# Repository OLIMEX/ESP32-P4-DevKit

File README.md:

# ESP32-P4-DevKit
Development board for ESP32-P4 Dual core RISCV processor from Espressif

https://www.olimex.com/Products/IoT/ESP32-P4/ESP32-P4-DevKit/open-source-hardware

## MIPI-LCD2.8 demos

The ESP-IDF MIPI display demos under `SOFTWARE/Demo_Examples` support both Olimex MIPI-LCD2.8 revisions. They default to WLK2802MIPI-15P-V2. See the per-demo readmes for build instructions and [CHANGELOG.md](CHANGELOG.md) for this revision's configuration changes.

## Licensee
* Hardware is released under CERN Open Hardware Licence Version 2 - Strongly Reciprocal
* Software is released under GPL V3 Licensee
* Documentation is released under CC BY-SA 4.0

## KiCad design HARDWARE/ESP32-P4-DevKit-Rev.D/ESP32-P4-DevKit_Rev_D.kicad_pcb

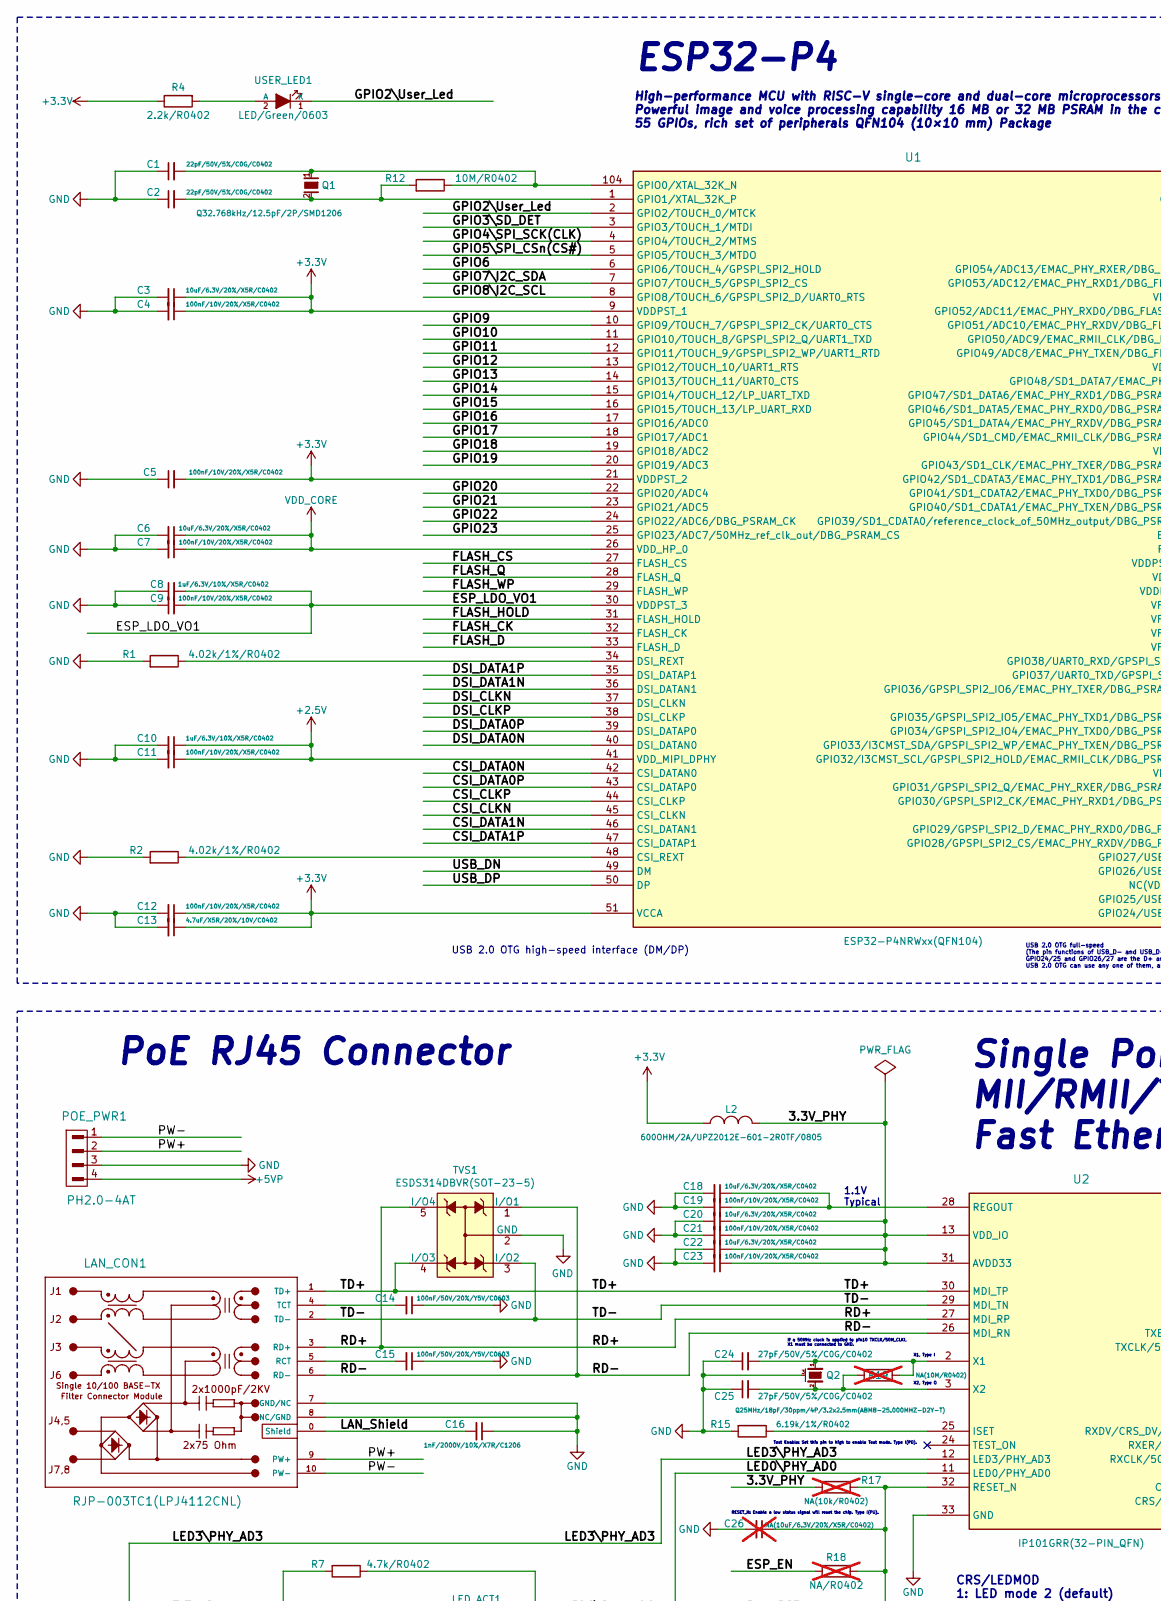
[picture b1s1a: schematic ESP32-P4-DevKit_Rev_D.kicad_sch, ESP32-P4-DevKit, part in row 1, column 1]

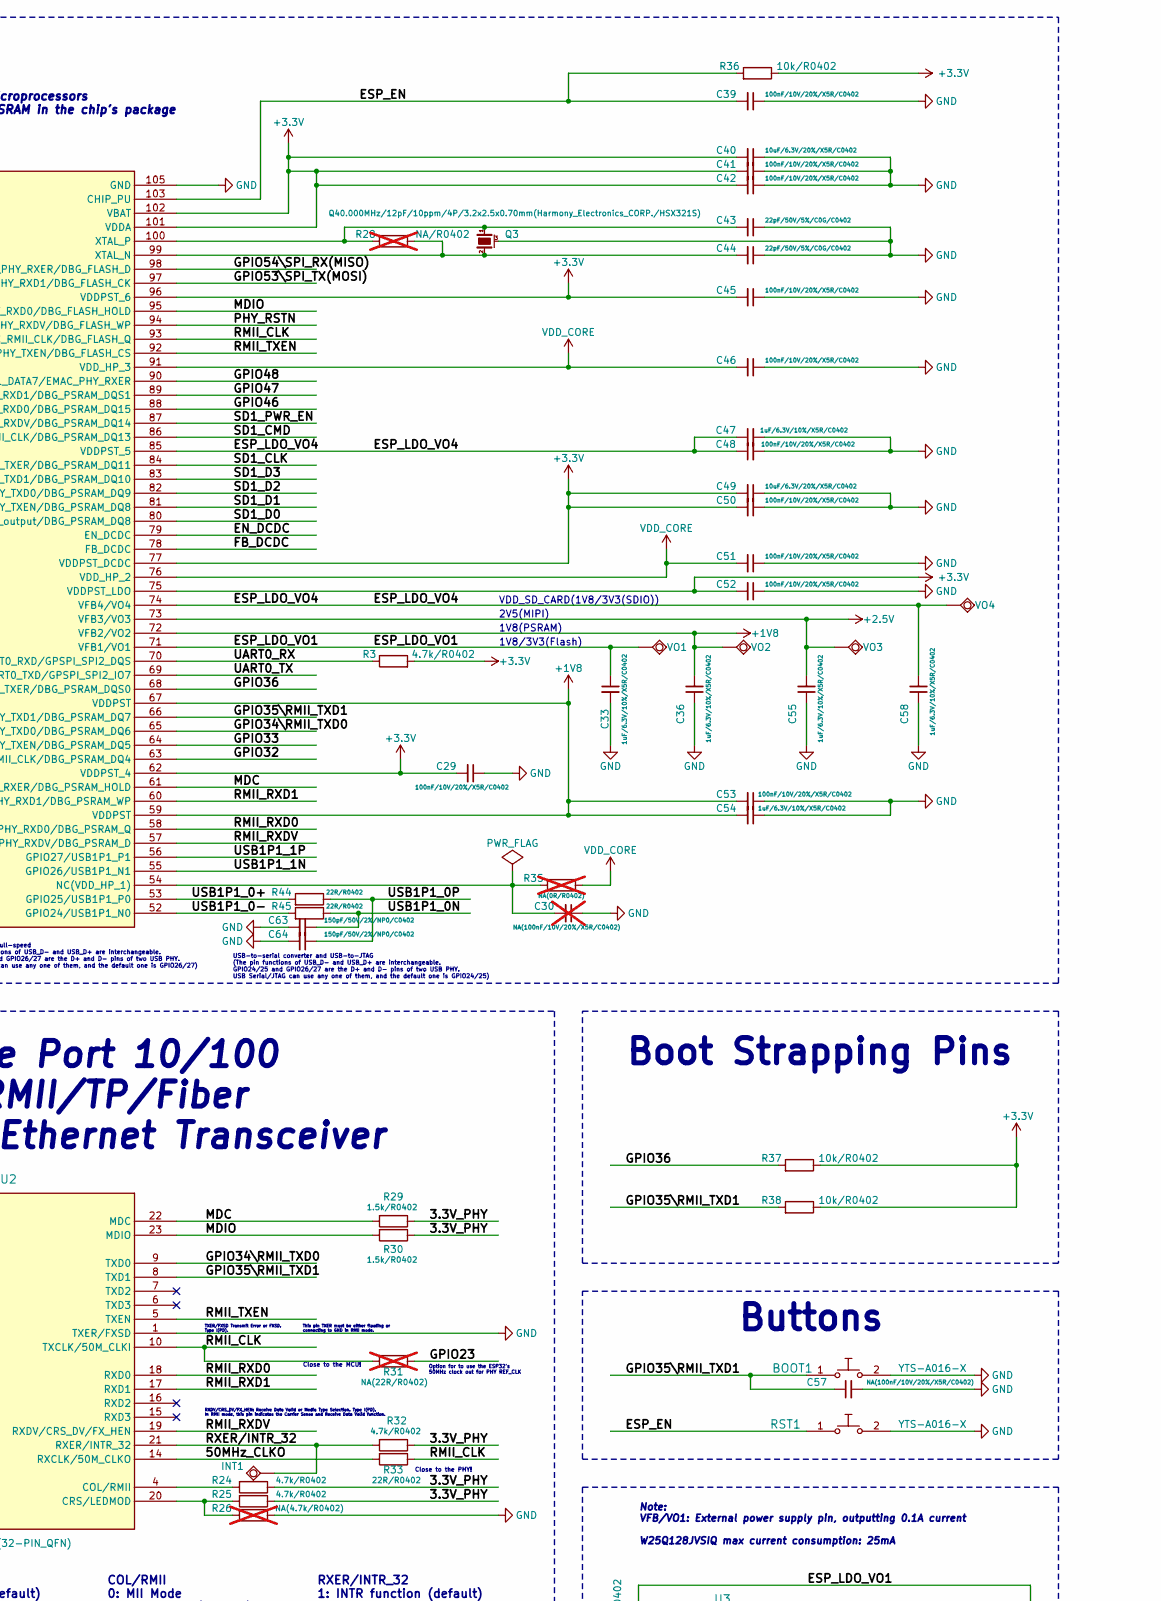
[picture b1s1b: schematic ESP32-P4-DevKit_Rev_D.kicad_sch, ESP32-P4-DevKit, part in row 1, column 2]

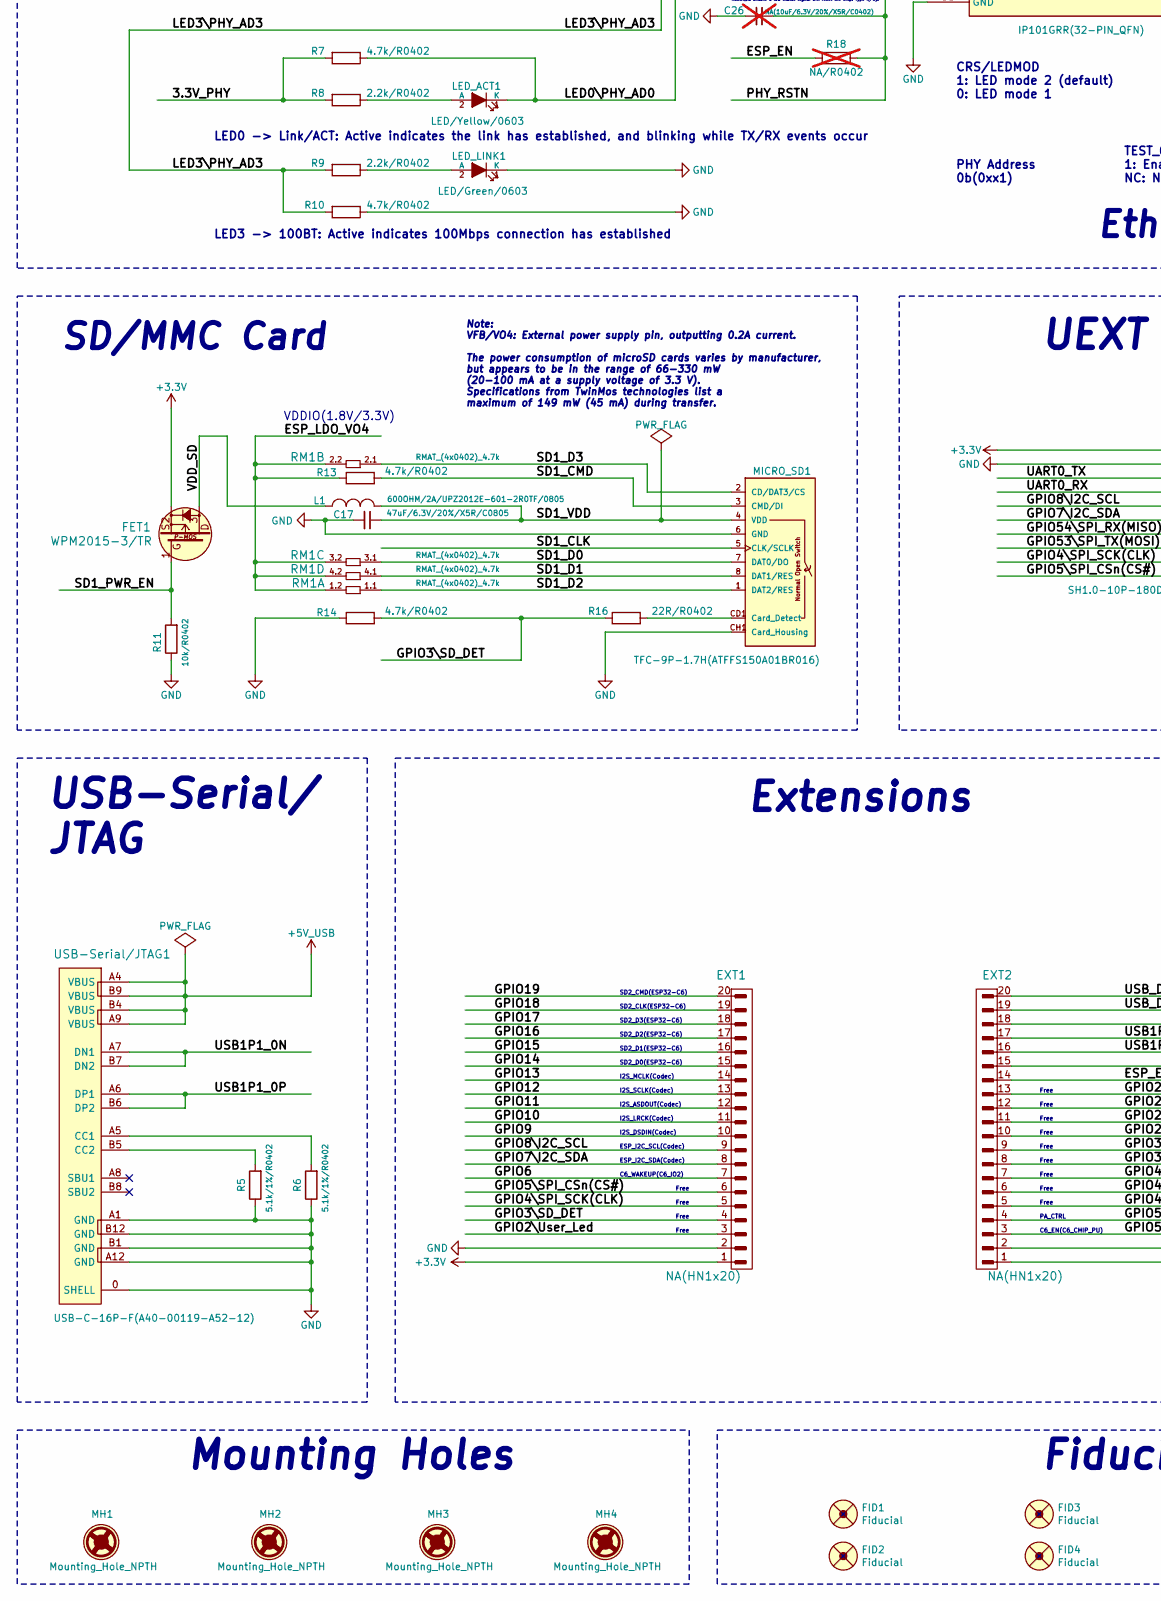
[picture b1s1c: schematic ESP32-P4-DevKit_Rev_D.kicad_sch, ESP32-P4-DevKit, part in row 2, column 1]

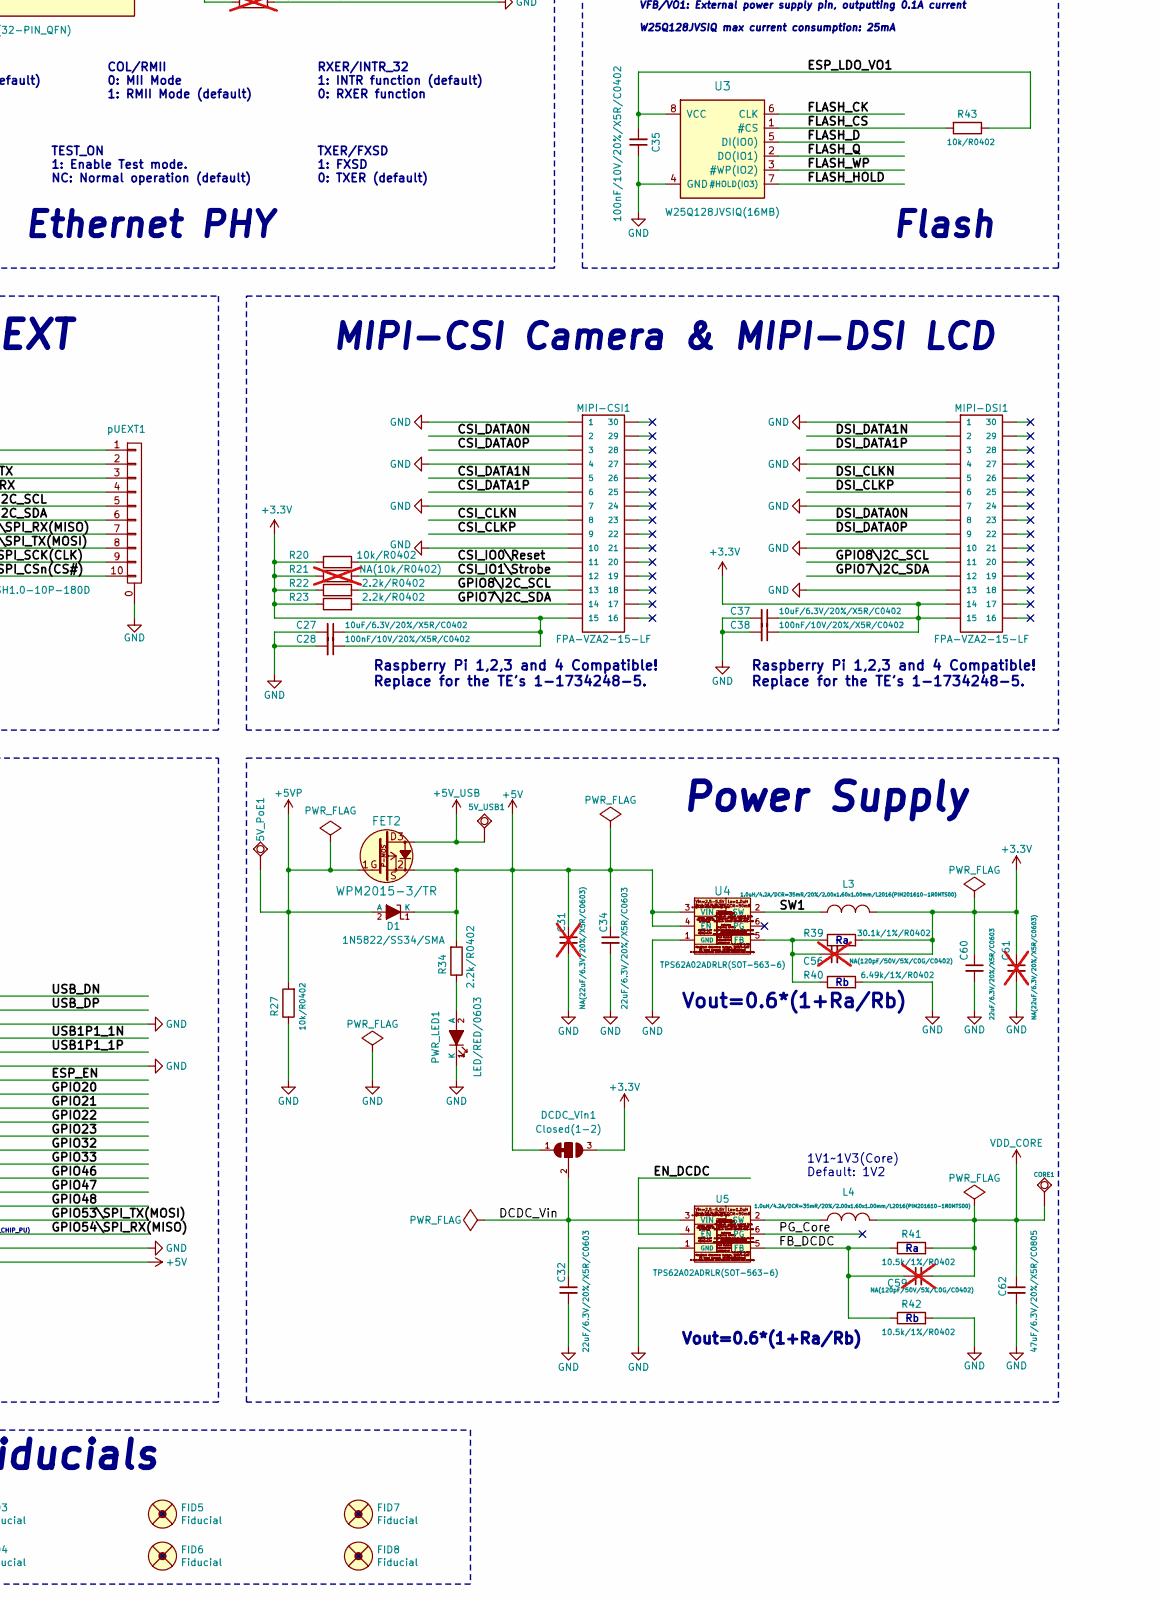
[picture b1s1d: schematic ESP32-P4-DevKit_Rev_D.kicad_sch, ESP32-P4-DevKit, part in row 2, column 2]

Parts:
5V_PoE1, 5V_USB1: TESTPAD; TESTPAD_40-ROUND
BOOT1: YTS-A016-X
C1, C2, C43, C44: 22pF/50V/5%/C0G/C0402; C_0402_5MIL_DWS
C3, C6, C18, C20, C22, C27, C37, C40, C49: 10uF/6.3V/20%/X5R/C0402; C_0402_5MIL_DWS
C4, C5, C7, C9, C11, C12, C19, C21, C23, C28, C29, C35, C38, C39, C41, C42, C45, C46, C48, C50, C51, C52, C53: 100nF/10V/20%/X5R/C0402; C_0402_5MIL_DWS
C8, C10, C33, C36, C47, C54, C55, C58: 1uF/6.3V/10%/X5R/C0402; C_0402_5MIL_DWS
C13: 4.7uF/X5R/20%/10V/C0402; C_0402_5MIL_DWS
C14, C15: 100nF/50V/20%/Y5V/C0603; C_0603_5MIL_DWS
C16: 1nF/2000V/10%/X7R/C1206; C_1206_5MIL_DWS_ISO
C17, C62: 47uF/6.3V/20%/X5R/C0805; C_0805_5MIL_DWS
C24, C25: 27pF/50V/5%/C0G/C0402; C_0402_5MIL_DWS
C26: NA(10uF/6.3V/20%/X5R/C0402); C_0402_5MIL_DWS; not fitted
C30: NA(100nF/10V/20%/X5R/C0402); C_0402_5MIL_DWS; not fitted
C31, C61: NA(22uF/6.3V/20%/X5R/C0603); C_0603_5MIL_DWS; not fitted
C32, C34, C60: 22uF/6.3V/20%/X5R/C0603; C_0603_5MIL_DWS
C56, C59: NA(120pF/50V/5%/C0G/C0402); C_0402_5MIL_DWS; not fitted
C57: NA(100nF/10V/20%/X5R/C0402); C_0402_5MIL_DWS
C63, C64: 150pF/50V/2%/NP0/C0402; C_0402_5MIL_DWS
CORE1: TESTPAD; TESTPAD_40-ROUND
D1: 1N5822/SS34/SMA; SMA-KA
DCDC_Vin1: Closed(1-2); SJ_2_SMALL_12_TIED
EXT1, EXT2: NA(HN1x20); HN1x20
FET1, FET2: WPM2015-3/TR; SOT23
FID1, FID3, FID5, FID7: Fiducial; Fiducial1x3
FID2, FID4, FID6, FID8: Fiducial; Fiducial1x3_Paste
INT1: TESTPAD; TESTPAD_40-ROUND
L1, L2: 600OHM/2A/UPZ2012E-601-2R0TF/0805; L_0805_5MIL_DWS
L3, L4: 1.0uH/4.2A/DCR=35mR/20%/2.00x1.60x1.00mm/L2016(PI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; L_2016_MM
LAN_CON1: RJP-003TC1(LPJ4112CNL)
LED_ACT1: LED/Yellow/0603; LED_0603_KA
LED_LINK1: LED/Green/0603; LED_0603_KA
MH1, MH2, MH3, MH4: Mounting_Hole_NPTH; Mounting_Hole_Drill-3.3mm_Clerance-7mm
MICRO_SD1: TFC-9P-1.7H(ATFFS150A01BR016); uSD(TFC-9P-1.xH(ATFFS150A01BR016))
MIPI-CSI1: FPA-VZA2-15-LF; TE_1-1734248-5
MIPI-DSI1: FPA-VZA2-15-LF; TE_1-1734248-5
POE_PWR1: PH2.0-4AT; PH2.0-4PLB
PWR_LED1: LED/RED/0603; LED_0603_KA
Q1: Q32.768kHz/12.5pF/2P/SMD1206; CM7V-T1A(Crystal_Package-1206_3.20x1.50x0.65mm)
Q2: Q25MHz/18pF/30ppm/4P/3.2x2.5mm(ABM8-25.000MHZ-D2Y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; TSX-3.2x2.5mm_GND(3)
Q3: Q40.000MHz/12pF/10ppm/4P/3.2x2.5x0.70mm(Harmony_E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; TSX-3.2x2.5mm_GND(3)
R1, R2: 4.02k/1%/R0402; R_0402_5MIL_DWS
R3, R7, R10, R13, R14, R24, R25, R32: 4.7k/R0402; R_0402_5MIL_DWS
R4, R8, R9, R22, R23, R34: 2.2k/R0402; R_0402_5MIL_DWS
R5, R6: 5.1k/1%/R0402; R_0402_5MIL_DWS
R11, R20, R27, R36, R37, R38, R43: 10k/R0402; R_0402_5MIL_DWS
R12: 10M/R0402; R_0402_5MIL_DWS
R15: 6.19k/1%/R0402; R_0402_5MIL_DWS
R16, R33, R44, R45: 22R/R0402; R_0402_5MIL_DWS
R17, R21: NA(10k/R0402); R_0402_5MIL_DWS; not fitted
R18, R28: NA/R0402; R_0402_5MIL_DWS; not fitted
R19: NA(10M/R0402); R_0402_5MIL_DWS; not fitted
R26: NA(4.7k/R0402); R_0402_5MIL_DWS; not fitted
R29, R30: 1.5k/R0402; R_0402_5MIL_DWS
R31: NA(22R/R0402); R_0402_5MIL_DWS; not fitted
R35: NA(0R/R0402); R_0402_5MIL_DWS; not fitted
R39: 30.1k/1%/R0402; R_0402_5MIL_DWS
R40: 6.49k/1%/R0402; R_0402_5MIL_DWS
R41, R42: 10.5k/1%/R0402; R_0402_5MIL_DWS
RM1: RMAT_(4x0402)_4.7k; RA0805_(4X0402)_xx_BIGGEROUTPADS
RST1: YTS-A016-X
TVS1: ESDS314DBVR(SOT-23-5); SOT-23-5
U1: ESP32-P4NRWxx(QFN104); QFN104_10mm×10mm_Pitch_0.35mm
U2: IP101GRR(32-PIN_QFN); QFN32_EP(33)_4.00x4.00x0.80mm_Pitch_0.40mm
U3: W25Q128JVSIQ(16MB); SO-8_208mil
U4, U5: TPS62A02ADRLR(SOT-563-6); SOT-563-6
USB-Serial/JTAG1: USB-C-16P-F(A40-00119-A52-12); USB2.0_TYPE-C(A40-00119-A52-12)_Paste
USER_LED1: LED/Green/0603; LED_0603_KA
VO1, VO2, VO3, VO4: TESTPAD; TESTPAD_40-ROUND
pUEXT1: SH1.0-10P-180D; BM10B-SRSS-TB

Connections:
+1V8: C36.2, C53.2, C54.2, U1.59 (VDDPST), U1.67 (VDDPST), U1.72 (VFB2/VO2), VO2.1 (Pad)
+2.5V: C10.1, C11.1, C55.2, U1.41 (VDD_MIPI_DPHY), U1.73 (VFB3/VO3), VO3.1 (Pad)
+3.3V: C3.1, C4.1, C5.2, C12.1, C13.1, C27.1, C28.1, C29.2, C37.1, C38.1, C40.2, C41.2, C42.2, C45.2, C49.2, C50.2, C52.2, C56.2, C60.1, C61.1, DCDC_Vin1.3, EXT1.1, FET1.2, L2.1, L3.2, MIPI-CSI1.15, MIPI-DSI1.14, MIPI-DSI1.15, R3.2, R4.1, R20.1, R21.1, R22.1, R23.1, R36.1, R37.1, R38.1, R39.2, U1.9 (VDDPST_1), U1.21 (VDDPST_2), U1.51 (VCCA), U1.62 (VDDPST_4), U1.75 (VDDPST_LDO), U1.77 (VDDPST_DCDC), U1.96 (VDDPST_6), U1.101 (VDDA), U1.102 (VBAT), pUEXT1.1
+5V: C31.1, C34.1, D1.1 (K), DCDC_Vin1.1, EXT2.1, FET2.2, R34.2, U4.3 (VIN), U4.4 (EN)
+5VP: 5V_PoE1.1 (Pad), D1.2 (A), FET2.1, POE_PWR1.4, R27.2
+5V_USB: 5V_USB1.1 (Pad), FET2.3, USB-Serial/JTAG1.A4 (VBUS), USB-Serial/JTAG1.A9 (VBUS), USB-Serial/JTAG1.B4 (VBUS), USB-Serial/JTAG1.B9 (VBUS)
/3.3V_PHY: C20.1, C21.1, C22.1, C23.1, L2.2, R7.2, R8.2, R17.1, R24.1, R25.1, R29.1, R30.1, R32.1, U2.13 (VDD_IO), U2.31 (AVDD33)
/50MHz_CLKO: R33.2, U2.14 (RXCLK/50M_CLKO)
/CSI_CLKN: MIPI-CSI1.8, U1.45 (CSI_CLKN)
/CSI_CLKP: MIPI-CSI1.9, U1.44 (CSI_CLKP)
/CSI_DATA0N: MIPI-CSI1.2, U1.42 (CSI_DATAN0)
/CSI_DATA0P: MIPI-CSI1.3, U1.43 (CSI_DATAP0)
/CSI_DATA1N: MIPI-CSI1.5, U1.46 (CSI_DATAN1)
/CSI_DATA1P: MIPI-CSI1.6, U1.47 (CSI_DATAP1)
/CSI_IO0\Reset: MIPI-CSI1.11, R20.2
/CSI_IO1\Strobe: MIPI-CSI1.12, R21.2
/DCDC_Vin: C32.1, DCDC_Vin1.2, U5.3 (VIN)
/DSI_CLKN: MIPI-DSI1.5, U1.37 (DSI_CLKN)
/DSI_CLKP: MIPI-DSI1.6, U1.38 (DSI_CLKP)
/DSI_DATA0N: MIPI-DSI1.8, U1.40 (DSI_DATAN0)
/DSI_DATA0P: MIPI-DSI1.9, U1.39 (DSI_DATAP0)
/DSI_DATA1N: MIPI-DSI1.2, U1.36 (DSI_DATAN1)
/DSI_DATA1P: MIPI-DSI1.3, U1.35 (DSI_DATAP1)
/EN_DCDC: U1.79 (EN_DCDC), U5.4 (EN)
/ESP_EN: C39.2, EXT2.14, R18.1, R36.2, RST1.1, U1.103 (CHIP_PU)
/ESP_LDO_VO1: C8.2, C9.2, C33.1, C35.2, R43.1, U1.30 (VDDPST_3), U1.71 (VFB1/VO1), U3.8 (VCC), VO1.1 (Pad)
/ESP_LDO_VO4: C47.1, C48.1, C58.2, R13.1, RM1.1.2, RM1.2.2, RM1.3.2, RM1.4.2, U1.74 (VFB4/VO4), U1.85 (VDDPST_5), VO4.1 (Pad)
/FB_DCDC: C59.1, R41.1, R42.1, U1.78 (FB_DCDC), U5.5 (FB)
/FLASH_CK: U1.32 (FLASH_CK), U3.6 (CLK)
/FLASH_CS: R43.2, U1.27 (FLASH_CS), U3.1 (#CS)
/FLASH_D: U1.33 (FLASH_D), U3.5 (DI(IO0))
/FLASH_HOLD: U1.31 (FLASH_HOLD), U3.7 (#HOLD(IO3))
/FLASH_Q: U1.28 (FLASH_Q), U3.2 (DO(IO1))
/FLASH_WP: U1.29 (FLASH_WP), U3.3 (#WP(IO2))
/GPIO2\User_Led: EXT1.3, U1.2 (GPIO2/TOUCH_0/MTCK), USER_LED1.1 (K)
/GPIO3\SD_DET: EXT1.4, R14.2, R16.1, U1.3 (GPIO3/TOUCH_1/MTDI)
/GPIO4\SPI_SCK(CLK): EXT1.5, U1.4 (GPIO4/TOUCH_2/MTMS), pUEXT1.9
/GPIO5\SPI_CSn(CS#): EXT1.6, U1.5 (GPIO5/TOUCH_3/MTDO), pUEXT1.10
/GPIO6: EXT1.7, U1.6 (GPIO6/TOUCH_4/GPSPI_SPI2_HOLD)
/GPIO7\I2C_SDA: EXT1.8, MIPI-CSI1.14, MIPI-DSI1.12, R23.2, U1.7 (GPIO7/TOUCH_5/GPSPI_SPI2_CS), pUEXT1.6
/GPIO8\I2C_SCL: EXT1.9, MIPI-CSI1.13, MIPI-DSI1.11, R22.2, U1.8 (GPIO8/TOUCH_6/GPSPI_SPI2_D/UART0_RTS), pUEXT1.5
/GPIO9: EXT1.10, U1.10 (GPIO9/TOUCH_7/GPSPI_SPI2_CK/UART0_CTS)
/GPIO10: EXT1.11, U1.11 (GPIO10/TOUCH_8/GPSPI_SPI2_Q/UART1_TXD)
/GPIO11: EXT1.12, U1.12 (GPIO11/TOUCH_9/GPSPI_SPI2_WP/UART1_RTD)
/GPIO12: EXT1.13, U1.13 (GPIO12/TOUCH_10/UART1_RTS)
/GPIO13: EXT1.14, U1.14 (GPIO13/TOUCH_11/UART0_CTS)
/GPIO14: EXT1.15, U1.15 (GPIO14/TOUCH_12/LP_UART_TXD)
/GPIO15: EXT1.16, U1.16 (GPIO15/TOUCH_13/LP_UART_RXD)
/GPIO16: EXT1.17, U1.17 (GPIO16/ADC0)
/GPIO17: EXT1.18, U1.18 (GPIO17/ADC1)
/GPIO18: EXT1.19, U1.19 (GPIO18/ADC2)
/GPIO19: EXT1.20, U1.20 (GPIO19/ADC3)
/GPIO20: EXT2.13, U1.22 (GPIO20/ADC4)
/GPIO21: EXT2.12, U1.23 (GPIO21/ADC5)
/GPIO22: EXT2.11, U1.24 (GPIO22/ADC6/DBG_PSRAM_CK)
/GPIO23: EXT2.10, R31.1, U1.25 (GPIO23/ADC7/50MHz_ref_clk_out/DBG_PSRAM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)
/GPIO32: EXT2.9, U1.63 (GPIO32/I3CMST_SCL/GPSPI_SPI2_HOLD/EMAC_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)
/GPIO33: EXT2.8, U1.64 (GPIO33/I3CMST_SDA/GPSPI_SPI2_WP/EMAC_PH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)
/GPIO34\RMII_TXD0: U1.65 (GPIO34/GPSPI_SPI2_IO4/EMAC_PHY_TXD0/DBG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), U2.9 (TXD0)
/GPIO35\RMII_TXD1: BOOT1.1, C57.1, R38.2, U1.66 (GPIO35/GPSPI_SPI2_IO5/EMAC_PHY_TXD1/DBG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), U2.8 (TXD1)
/GPIO36: R37.2, U1.68 (GPIO36/GPSPI_SPI2_IO6/EMAC_PHY_TXER/DBG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)
/GPIO46: EXT2.7, U1.88 (GPIO46/SD1_DATA5/EMAC_PHY_RXD0/DBG_PSRA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)
/GPIO47: EXT2.6, U1.89 (GPIO47/SD1_DATA6/EMAC_PHY_RXD1/DBG_PSRA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)
/GPIO48: EXT2.5, U1.90 (GPIO48/SD1_DATA7/EMAC_PHY_RXER)
/GPIO53\SPI_TX(MOSI): EXT2.4, U1.97 (GPIO53/ADC12/EMAC_PHY_RXD1/DBG_FLASH_CK), pUEXT1.8
/GPIO54\SPI_RX(MISO): EXT2.3, U1.98 (GPIO54/ADC13/EMAC_PHY_RXER/DBG_FLASH_D), pUEXT1.7
/LAN_Shield: C16.2, LAN_CON1.0 (Shield)
/LED0\PHY_AD0: LED_ACT1.1 (K), R7.1, U2.11 (LED0/PHY_AD0)
/LED3\PHY_AD3: R9.2, R10.2, U2.12 (LED3/PHY_AD3)
/MDC: R29.2, U1.61 (GPIO31/GPSPI_SPI2_Q/EMAC_PHY_RXER/DBG_P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), U2.22 (MDC)
/MDIO: R30.2, U1.95 (GPIO52/ADC11/EMAC_PHY_RXD0/DBG_FLASH_HO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), U2.23 (MDIO)
/PG_Core: U5.6 (PG)
/PHY_RSTN: C26.1, R17.2, R18.2, U1.94 (GPIO51/ADC10/EMAC_PHY_RXDV/DBG_FLASH_WP), U2.32 (RESET_N)
/PW+: LAN_CON1.9 (PW+), POE_PWR1.2
/PW-: LAN_CON1.10 (PW-), POE_PWR1.1
/RD+: LAN_CON1.3 (RD+), TVS1.5 (I/O4), U2.27 (MDI_RP)
/RD-: LAN_CON1.6 (RD-), TVS1.1 (I/O1), U2.26 (MDI_RN)
/RMII_CLK: R31.2, R33.1, U1.93 (GPIO50/ADC9/EMAC_RMII_CLK/DBG_FLASH_Q), U2.10 (TXCLK/50M_CLKI)
/RMII_RXD0: U1.58 (GPIO29/GPSPI_SPI2_D/EMAC_PHY_RXD0/DBG_P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), U2.18 (RXD0)
/RMII_RXD1: U1.60 (GPIO30/GPSPI_SPI2_CK/EMAC_PHY_RXD1/DBG_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), U2.17 (RXD1)
/RMII_RXDV: U1.57 (GPIO28/GPSPI_SPI2_CS/EMAC_PHY_RXDV/DBG_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), U2.19 (RXDV/CRS_DV/FX_HEN)
/RMII_TXEN: U1.92 (GPIO49/ADC8/EMAC_PHY_TXEN/DBG_FLASH_CS), U2.5 (TXEN)
/RXER/INTR_32: INT1.1 (Pad), R32.2, U2.21 (RXER/INTR_32)
/SD1_CLK: MICRO_SD1.5 (CLK/SCLK), U1.84 (GPIO43/SD1_CLK/EMAC_PHY_TXER/DBG_PSRAM_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)
/SD1_CMD: MICRO_SD1.3 (CMD/DI), R13.2, U1.86 (GPIO44/SD1_CMD/EMAC_RMII_CLK/DBG_PSRAM_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)
/SD1_D0: MICRO_SD1.7 (DAT0/DO), RM1.3.1, U1.80 (GPIO39/SD1_CDATA0/reference_clock_of_50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)
/SD1_D1: MICRO_SD1.8 (DAT1/RES), RM1.4.1, U1.81 (GPIO40/SD1_CDATA1/EMAC_PHY_TXEN/DBG_PSR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)
/SD1_D2: MICRO_SD1.1 (DAT2/RES), RM1.1.1, U1.82 (GPIO41/SD1_CDATA2/EMAC_PHY_TXD0/DBG_PSR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)
/SD1_D3: MICRO_SD1.2 (CD/DAT3/CS), RM1.2.1, U1.83 (GPIO42/SD1_CDATA3/EMAC_PHY_TXD1/DBG_PSR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)
/SD1_PWR_EN: FET1.1, R11.2, U1.87 (GPIO45/SD1_DATA4/EMAC_PHY_RXDV/DBG_PSRA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)
/SD1_VDD: C17.1, L1.2, MICRO_SD1.4 (VDD)
/SW1: L3.1, U4.2 (SW)
/TD+: LAN_CON1.1 (TD+), TVS1.4 (I/O3), U2.30 (MDI_TP)
/TD-: LAN_CON1.2 (TD-), TVS1.3 (I/O2), U2.29 (MDI_TN)
/UART0_RX: R3.1, U1.70 (GPIO38/UART0_RXD/GPSPI_SPI2_DQS), pUEXT1.4
/UART0_TX: U1.69 (GPIO37/UART0_TXD/GPSPI_SPI2_IO7), pUEXT1.3
/USB1P1_0+: R44.2, U1.53 (GPIO25/USB1P1_P0)
/USB1P1_0-: R45.2, U1.52 (GPIO24/USB1P1_N0)
/USB1P1_0N: C63.1, R45.1, USB-Serial/JTAG1.A7 (DN1), USB-Serial/JTAG1.B7 (DN2)
/USB1P1_0P: C64.1, R44.1, USB-Serial/JTAG1.A6 (DP1), USB-Serial/JTAG1.B6 (DP2)
/USB1P1_1N: EXT2.17, U1.55 (GPIO26/USB1P1_N1)
/USB1P1_1P: EXT2.16, U1.56 (GPIO27/USB1P1_P1)
/USB_DN: EXT2.20, U1.49 (DM)
/USB_DP: EXT2.19, U1.50 (DP)
/VDD_SD: FET1.3, L1.1
GND: BOOT1.2, C1.1, C2.1, C3.2, C4.2, C5.1, C6.2, C7.2, C8.1, C9.1, C10.2, C11.2, C12.2, C13.2, C14.1, C15.1, C16.1, C17.2, C18.2, C19.2, C20.2, C21.2, C22.2, C23.2, C24.1, C25.1, C26.2, C27.2, C28.2, C29.1, C30.1, C31.2, C32.2, C33.2, C34.2, C35.1, C36.1, C37.2, C38.2, C39.1, C40.1, C41.1, C42.1, C43.1, C44.1, C45.1, C46.1, C47.2, C48.2, C49.1, C50.1, C51.1, C52.1, C53.1, C54.1, C55.1, C57.2, C58.1, C60.2, C61.2, C62.2, C63.2, C64.2, EXT1.2, EXT2.2, EXT2.15, EXT2.18, LAN_CON1.7 (GND/NC), LAN_CON1.8 (NC/GND), LED_LINK1.1 (K), MICRO_SD1.6 (GND), MICRO_SD1.CH1 (Card_Housing), MIPI-CSI1.1, MIPI-CSI1.4, MIPI-CSI1.7, MIPI-CSI1.10, MIPI-DSI1.1, MIPI-DSI1.4, MIPI-DSI1.7, MIPI-DSI1.10, MIPI-DSI1.13, POE_PWR1.3, PWR_LED1.1 (K), Q2.3 (case), Q3.3 (case), R1.2, R2.2, R5.1, R6.1, R10.1, R11.1, R14.1, R15.2, R26.1, R27.1, R40.2, R42.2, RST1.2, TVS1.2 (GND), U1.105 (GND), U2.1 (TXER/FXSD), U2.33 (GND), U3.4 (GND), U4.1 (GND), U5.1 (GND), USB-Serial/JTAG1.0 (SHELL), USB-Serial/JTAG1.A1 (GND), USB-Serial/JTAG1.A12 (GND), USB-Serial/JTAG1.B1 (GND), USB-Serial/JTAG1.B12 (GND), pUEXT1.0, pUEXT1.2
unnamed: C15.2, LAN_CON1.5 (RCT)
unnamed: C14.2, LAN_CON1.4 (TCT)
unnamed: LED_ACT1.2 (A), R8.1
unnamed: LED_LINK1.2 (A), R9.1
unnamed: MICRO_SD1.CD1 (Card_Detect), R16.2
unnamed: PWR_LED1.2 (A), R34.1
unnamed: R2.1, U1.48 (CSI_REXT)
unnamed: R1.1, U1.34 (DSI_REXT)
unnamed: C1.2, Q1.1, R12.1, U1.104 (GPIO0/XTAL_32K_N)
unnamed: C2.2, Q1.2, R12.2, U1.1 (GPIO1/XTAL_32K_P)
unnamed: C30.2, R35.2, U1.54 (NC(VDD_HP_1))
unnamed: C44.2, Q3.2, R28.2, U1.99 (XTAL_N)
unnamed: C43.2, Q3.1, R28.1, U1.100 (XTAL_P)
unnamed: R24.2, U2.4 (COL/RMII)
unnamed: R25.2, R26.2, U2.20 (CRS/LEDMOD)
unnamed: R15.1, U2.25 (ISET)
unnamed: C18.1, C19.1, U2.28 (REGOUT)
unnamed: C24.2, Q2.1, R19.2, U2.2 (X1)
unnamed: C25.2, Q2.2, R19.1, U2.3 (X2)
unnamed: C56.1, R39.1, R40.1, U4.5 (FB)
unnamed: L4.1, U5.2 (SW)
unnamed: R6.2, USB-Serial/JTAG1.A5 (CC1)
unnamed: R5.2, USB-Serial/JTAG1.B5 (CC2)
unnamed: R4.2, USER_LED1.2 (A)
VDD_CORE: C6.1, C7.1, C46.2, C51.2, C59.2, C62.1, CORE1.1 (Pad), L4.2, R35.1, R41.2, U1.26 (VDD_HP_0), U1.76 (VDD_HP_2), U1.91 (VDD_HP_3)

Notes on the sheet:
Note: VFB/VO1: External power supply pin, outputting 0.1A current W25Q128JVSIQ max current consumption: 25mA
TXER/FXSD Transmit Error or FXSD. Type I(PD).
I2S_LRCK(Codec)
USB-to-serial converter and USB-to-JTAG (The pin functions of USB_D- and USB_D+ are interchangeable. GPIO24/25 and GPIO26/27 are the D+ and D- pins of two USB PHY. USB Serial/JTAG can use any one of them, and the default one is GPIO24/25)
Power Supply
Vout=0.6*(1+Ra/Rb)
I2S_DSDIN(Codec)
Free
SD2_D2(ESP32-C6)
Boot Strapping Pins
Mounting Holes
LED0 -> Link/ACT: Active indicates the link has established, and blinking while TX/RX events occur
SD2_D1(ESP32-C6)
RXER/INTR_32 1: INTR function (default) 0: RXER function
COL/RMII 0: MII Mode 1: RMII Mode (default)
This pin TXER must be either floating or connecting to GND in RMII mode.
I2S_SCLK(Codec)
Close to the MCU!
RXDV/CRS_DV/FX_HEN: Receive Data Valid or Media Type Selection. Type I(PD). In RMII mode, this pin indicates the Carrier Sense and Receive Data Valid function.
SD2_CLK(ESP32-C6)
TXER/FXSD 1: FXSD 0: TXER (default)
TEST_ON 1: Enable Test mode. NC: Normal operation (default)
Ethernet PHY
SD2_CMD(ESP32-C6)
Test Enable: Set this pin to high to enable Test mode. Type I(PD).
High-performance MCU with RISC-V single-core and dual-core microprocessors Powerful image and voice processing capability 16 MB or 32 MB PSRAM in the chip's package 55 GPIOs, rich set of peripherals QFN104 (10×10 mm) Package
USB 2.0 OTG high-speed interface (DM/DP)
If a 50MHz clock is applied to pin10 TXCLK/50M_CLKI, X1 must be connected to GND.
1V8/3V3(Flash)
X2, Type O
SD2_D0(ESP32-C6)
PoE RJ45 Connector
MIPI-CSI Camera & MIPI-DSI LCD
Raspberry Pi 1,2,3 and 4 Compatible! Replace for the TE's 1-1734248-5.
RESET_N: Enable a low status signal will reset the chip. Type I(PU).
I2S_ASDOUT(Codec)
C6_WAKEUP(C6_IO2)
USB 2.0 OTG full-speed (The pin functions of USB_D- and USB_D+ are interchangeable. GPIO24/25 and GPIO26/27 are the D+ and D- pins of two USB PHY. USB 2.0 OTG can use any one of them, and the default one is GPIO26/27)
Flash
Buttons

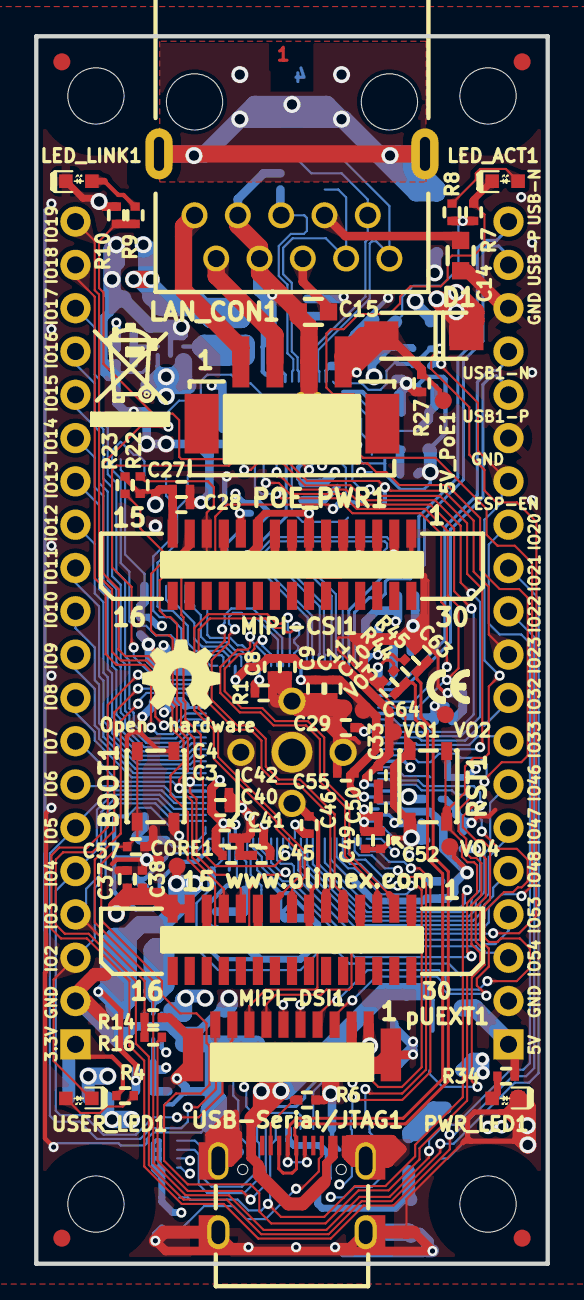
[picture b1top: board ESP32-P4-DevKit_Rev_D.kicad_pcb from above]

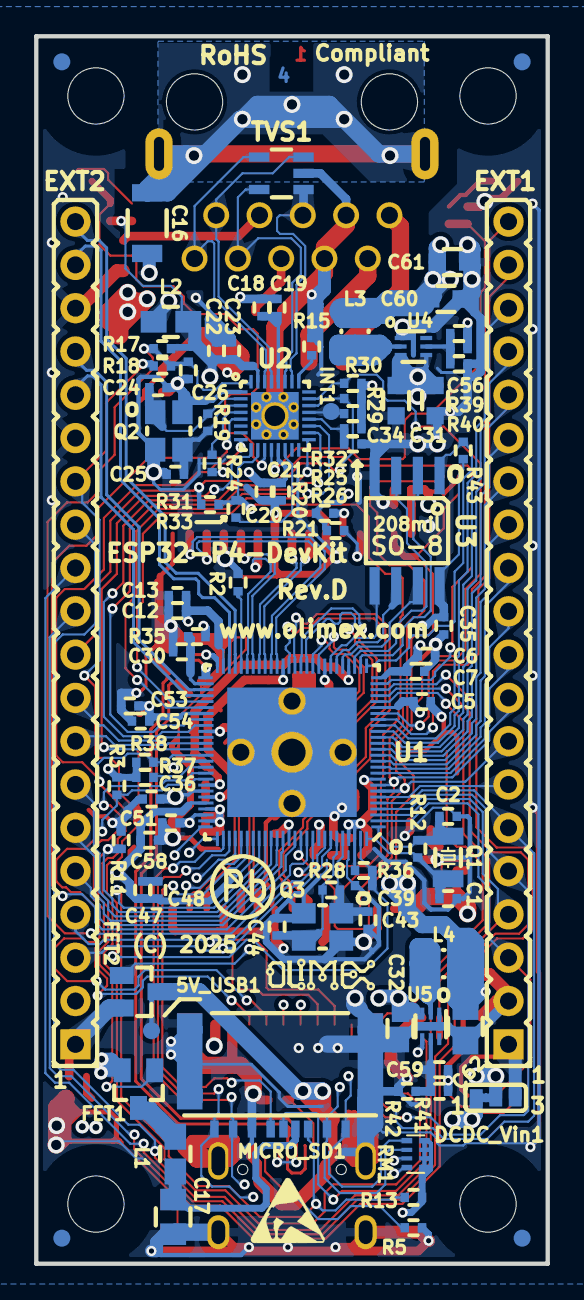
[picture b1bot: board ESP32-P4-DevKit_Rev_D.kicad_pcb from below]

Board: 4 copper layers, 30.0 x 72.0 mm, 168 parts (97 on the bottom side), 130 nets.

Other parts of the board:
Logo_OLIMEX_SMALL_TB: Logo_OLIMEX_SMALL_TB
Sign_Antistatic_150: Sign_Antistatic_150
Sign_CE_Small: CE_Sign_Small
Sign_OSHW_7.3x6.0mm: Sign_OSHW_7.3x6.0mm; Sign_OSHW_7.3x6.0mmn
Sign_PB-Free: Sign_PB-Free
Sign_RecycleBin_1: Sign_RecycleBin_1

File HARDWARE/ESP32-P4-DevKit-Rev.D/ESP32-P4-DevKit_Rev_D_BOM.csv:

Quantity,Value,Footprint,Reference
2,YTS-A016-X,YTS-A016-X,"BOOT1, RST1"
4,22pF/50V/5%/C0G/C0402,C_0402_5MIL_DWS,"C1, C2, C43, C44"
9,10uF/6.3V/20%/X5R/C0402,C_0402_5MIL_DWS,"C3, C6, C18, C20, C22, C27, C37, C40, C49"
23,100nF/10V/20%/X5R/C0402,C_0402_5MIL_DWS,"C4, C5, C7, C9, C11, C12, C19, C21, C23, C28, C29, C35, C38, C39, C41, C42, C45, C46, C48, C50, C51, C52, C53"
8,1uF/6.3V/10%/X5R/C0402,C_0402_5MIL_DWS,"C8, C10, C33, C36, C47, C54, C55, C58"
1,4.7uF/X5R/20%/10V/C0402,C_0402_5MIL_DWS,C13
2,100nF/50V/20%/Y5V/C0603,C_0603_5MIL_DWS,"C14, C15"
1,1nF/2000V/10%/X7R/C1206,C_1206_5MIL_DWS_ISO,C16
2,47uF/6.3V/20%/X5R/C0805,C_0805_5MIL_DWS,"C17, C62"
2,27pF/50V/5%/C0G/C0402,C_0402_5MIL_DWS,"C24, C25"
3,22uF/6.3V/20%/X5R/C0603,C_0603_5MIL_DWS,"C32, C34, C60"
2,150pF/50V/2%/NP0/C0402,C_0402_5MIL_DWS,"C63, C64"
1,1N5822/SS34/SMA,SMA-KA,D1
2,WPM2015-3/TR,SOT23,"FET1, FET2"
2,600OHM/2A/UPZ2012E-601-2R0TF/0805,L_0805_5MIL_DWS,"L1, L2"
2,1.0uH/4.2A/DCR=35mR/20%/2.00x1.60x1.00mm/L2016(PIM201610-1R0MTS00),L_2016_MM,"L3, L4"
1,RJP-003TC1(LPJ4112CNL),RJP-003TC1(LPJ4112CNL),LAN_CON1
1,LED/Yellow/0603,LED_0603_KA,LED_ACT1
2,LED/Green/0603,LED_0603_KA,"LED_LINK1, USER_LED1"
1,TFC-9P-1.7H(ATFFS150A01BR016),uSD(TFC-9P-1.xH(ATFFS150A01BR016)),MICRO_SD1
2,FPA-VZA2-15-LF,TE_1-1734248-5,"MIPI-CSI1, MIPI-DSI1"
1,PH2.0-4AT,PH2.0-4PLB,POE_PWR1
1,LED/RED/0603,LED_0603_KA,PWR_LED1
1,Q32.768kHz/12.5pF/2P/SMD1206,CM7V-T1A(Crystal_Package-1206_3.20x1.50x0.65mm),Q1
1,Q25MHz/18pF/30ppm/4P/3.2x2.5mm(ABM8-25.000MHZ-D2Y-T),TSX-3.2x2.5mm_GND(3),Q2
1,Q40.000MHz/12pF/10ppm/4P/3.2x2.5x0.70mm(Harmony_Electronics_CORP./HSX321S),TSX-3.2x2.5mm_GND(3),Q3
2,4.02k/1%/R0402,R_0402_5MIL_DWS,"R1, R2"
8,4.7k/R0402,R_0402_5MIL_DWS,"R3, R7, R10, R13, R14, R24, R25, R32"
6,2.2k/R0402,R_0402_5MIL_DWS,"R4, R8, R9, R22, R23, R34"
2,5.1k/1%/R0402,R_0402_5MIL_DWS,"R5, R6"
7,10k/R0402,R_0402_5MIL_DWS,"R11, R20, R27, R36, R37, R38, R43"
1,10M/R0402,R_0402_5MIL_DWS,R12
1,6.19k/1%/R0402,R_0402_5MIL_DWS,R15
4,22R/R0402,R_0402_5MIL_DWS,"R16, R33, R44, R45"
2,1.5k/R0402,R_0402_5MIL_DWS,"R29, R30"
1,30.1k/1%/R0402,R_0402_5MIL_DWS,R39
1,6.49k/1%/R0402,R_0402_5MIL_DWS,R40
2,10.5k/1%/R0402,R_0402_5MIL_DWS,"R41, R42"
1,RMAT_(4x0402)_4.7k,RA0805_(4X0402)_xx_BIGGEROUTPADS,RM1
1,ESDS314DBVR(SOT-23-5),SOT-23-5,TVS1
1,ESP32-P4NRWxx(QFN104),QFN104_10mm×10mm_Pitch_0.35mm,U1
1,IP101GRR(32-PIN_QFN),QFN32_EP(33)_4.00x4.00x0.80mm_Pitch_0.40mm,U2
1,W25Q128JVSIQ(16MB),SO-8_208mil,U3
2,TPS62A02ADRLR(SOT-563-6),SOT-563-6,"U4, U5"
1,USB-C-16P-F(A40-00119-A52-12),USB2.0_TYPE-C(A40-00119-A52-12)_Paste,USB-Serial/JTAG1
1,SH1.0-10P-180D,BM10B-SRSS-TB,pUEXT1

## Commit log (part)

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2024-12-13 initial upload
2024-12-16 add demo examples
2025-04-14 Update
    Hardware revision C
2025-06-09 Update
    New demo examples
2025-06-09 Update
    Added instructions for mipi_csi_dsi project.
2025-10-14 Update
    revision 2 of the manual
2025-12-03 Update
    HDMI demo with MIPI-HDMI adapter
2026-03-18 Update
    Added ESP32-P4-DevKit-Lipo examples for Arduino IDE
2026-04-03 Update
    Manual update
2026-06-26 Update
    Added documents for revisions D and D1
